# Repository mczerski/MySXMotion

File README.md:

# MySXMotion
## MySX Board for motion sensor

This is a multipurpose daughterboard but its main use is for AS312 motion sensor with MySX conector. It also consist of BH1750 ambient light sensor and header for one i2c device, uart and avr ISP. It is meant to be combined with a [MySMotherboard](https://www.openhardware.io/view/606/MySMotherboard) to make fully functional motion sensor node.

## Features:

1. support for SMD MySX header for low profile connection with MySX motherboard
2. AS312 motion sensor with dedicated LDO
3. BH1750 ambient light sensor
4. I2C header
5. AVR ISP header
6. uart header

## HOW TO
1. Low profile MySX header connector.
The board is designed for smd low profile MySX 2.5 header connector which significantly reduces node size. 

2. AS312 motion sensor
For best performance motion sensor is powered through dedicated low quiescent current 3V LDO. The LDO is powered from MySX VRAW pin, so voltage on this pin must be higer than 3.1V. 3.7V LI-ION rechargable battery would be a good power source solution. The circuit consists also of battery reverse polarity protecion MOSFET.
For motion sensor required components to solder are:
Q1, C1, C2, C3, R1, IC1, IC3

3. BH1750 ambient light sensor
Ambient light sensor is powered from the MySX VCC pin. J2 jumper is used to select I2C addres of the light sensor.
Required components to solder are:
R2, R3, R4, C4, C5, IC2, J1 (choose one of two options)

4. Additional headers
By soldering ISP header this board can be use as a MySX to AVR ISP adapter. To I2C header one additional i2c device can be conected. To UART header one additional uart device can be connected.

## Software
For easy software developement there is available toolkit library that enhance MySensors library called [MySensorsToolkit](https://github.com/mczerski/MySensorsToolkit) and also there is an example sketch [MyMultiSensor](https://github.com/mczerski/MyMultiSensor).
The easies way to use this software is to clone the current version of the Arduino sketchbook [Arduino-MySensors](https://github.com/mczerski/Arduino-MySensors):
```
git clone https://github.com/mczerski/Arduino-MySensors
git submodule update --init
```
and then setup Arduino IDE to point to this folder as a sketchbook.

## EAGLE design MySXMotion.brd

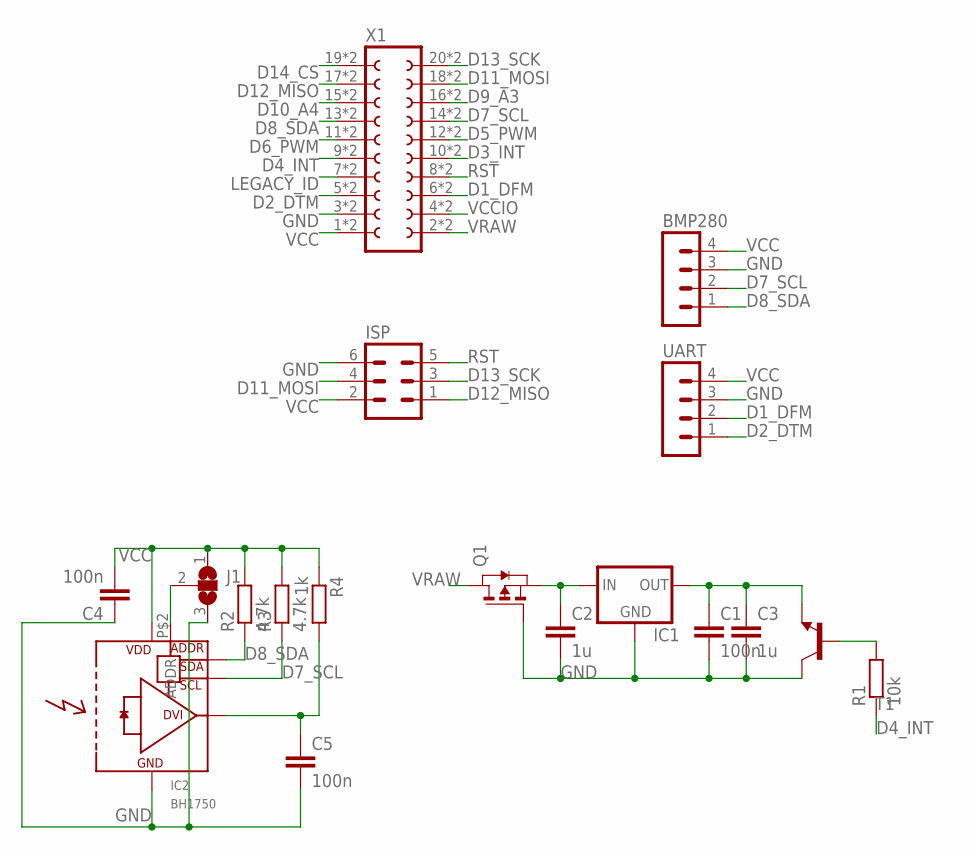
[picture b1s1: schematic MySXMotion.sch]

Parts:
BMP280: MA04-1
C1, C4, C5: 100n; C0603
C2: 1u; C0603
C3: 1u; C0805
IC1: XC63FPM; SOT23
IC2: BH1750; WSOF6
ISP: MA03-2
J1: SJ2W; SJ_2
Q1: PMOSSOT23; SOT-23
R1: 10k; R0603
R2, R3: 4.7k; R0603
R4: 1k; R0603
T1: -NPN-TO5; TO5
UART: MA04-1
X1: FE10-2

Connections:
D1_DFM: UART.2, X1.6, X1.P$6 (6)
D2_DTM: UART.1, X1.5, X1.P$5 (5)
D3_INT: X1.10, X1.P$10 (10)
D4_INT: R1.1, X1.9, X1.P$9 (9)
D5_PWM: X1.12, X1.P$12 (12)
D6_PWM: X1.11, X1.P$11 (11)
D7_SCL: BMP280.2, IC2.P$6 (SCL), R3.1, X1.14, X1.P$14 (14)
D8_SDA: BMP280.1, IC2.P$4 (SDA), R2.1, X1.13, X1.P$13 (13)
D9_A3: X1.16, X1.P$16 (16)
D10_A4: X1.15, X1.P$15 (15)
D11_MOSI: ISP.4, X1.18, X1.P$18 (18)
D12_MISO: ISP.1, X1.17, X1.P$17 (17)
D13_SCK: ISP.3, X1.20, X1.P$20 (20)
D14_CS: X1.19, X1.P$19 (19)
GND: BMP280.3, C1.2, C2.2, C3.2, C4.1, C5.2, IC1.1 (GND), IC2.P$3 (GND), ISP.6, J1.3, Q1.3 (G), T1.3 (C), UART.3, X1.3, X1.P$3 (3)
LEGACY_ID: X1.7, X1.P$7 (7)
unnamed: C5.1, IC2.P$5 (DVI), R4.2
unnamed: IC2.P$2 (ADDR), J1.2
unnamed: R1.2, T1.2 (B)
unnamed: C2.1, IC1.3 (IN), Q1.2 (S)
unnamed: C1.1, C3.1, IC1.2 (OUT), T1.1 (E)
RST: ISP.5, X1.8, X1.P$8 (8)
VCC: BMP280.4, C4.2, IC2.P$1 (VCC), ISP.2, J1.1, R2.2, R3.2, R4.1, UART.4, X1.1, X1.P$1 (1)
VCCIO: X1.4, X1.P$4 (4)
VRAW: Q1.1 (D), X1.2, X1.P$2 (2)

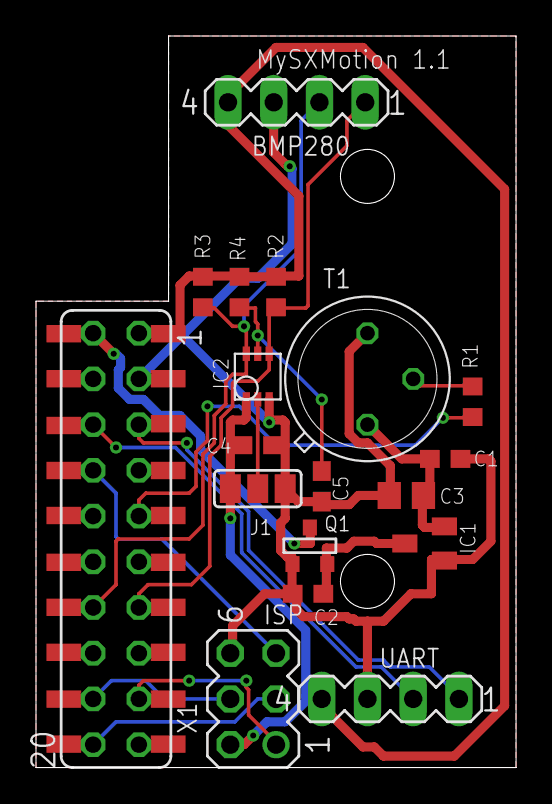
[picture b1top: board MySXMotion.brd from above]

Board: 2 copper layers, 26.7 x 40.6 mm, 18 parts (0 on the bottom side), 25 nets.

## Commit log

2018-06-10 firs version
2018-07-07 add reverse voltage protection
2018-07-24 add documentation
2018-07-24 add bom and schematic pdf
2018-07-24 update documentation
